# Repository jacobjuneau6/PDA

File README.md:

# ESP32-S3 PDA

A simple ESP32-S3 based phone companion and pocket computer. This open-source hardware project includes a custom PCB, 3D-printable case, and Arduino firmware — everything you need to build a portable device with a color TFT display, LiPo battery management, and physical navigation buttons.

## Features

- **ESP32-S3-WROOM-1-N16R8** module (16 MB flash, 8 MB PSRAM)
- **ST7789 240×320 TFT** color display with PWM backlight control
- **MAX17048** LiPo fuel gauge for accurate battery state-of-charge
- **MCP73831** Li-Ion/Li-Po battery charger (charges via USB)
- **WS2812/NeoPixel** RGB status LED
- **3 navigation buttons** (UP, SELECT, DOWN) with active-low pull-ups
- **USB micro-B** connector for power and data
- **2-layer PCB** with Gerber files ready for fabrication
- **3D-printable case** designed in FreeCAD

## Pinout

| Silkscreen | GPIO | Function |
|-----------|------|----------|
| SCL | 2 | SPI SCLK (TFT clock) |
| SDA | 1 | SPI MOSI (TFT data) |
| CS | 3 | TFT chip select |
| DC | 4 | TFT data/command |
| RST | 5 | TFT reset |
| BL | 6 | TFT backlight PWM |
| — | 7 | WS2812 status LED (NeoPixel) |
| — | 8 | I2C SCL (MAX17048 fuel gauge) |
| — | 9 | I2C SDA (MAX17048 fuel gauge) |
| — | 10 | Button UP |
| — | 11 | Button SELECT |
| — | 12 | Button DOWN |

**Display connector:** 1×08 pin header (GND, VCC, SCL, SDA, RST, DC, CS, BL) for ST7789 240×320 TFT, 1.54″ or 1.69″ diagonal.

**I²C address:** MAX17048 at `0x36`.

## Bill of Materials

| Reference            | Qty | Part                    | DigiKey P/N              | Description                                                | Price  |
|---------------------|-----|-------------------------|--------------------------|------------------------------------------------------------|--------|
| J1                  | 1   | RAHMB20AUETR            | 137-RAHMB20AUETRCT-ND    | USB micro-B receptacle, right-angle, SMT (Switchcraft)     |        |
| LED1                | 1   | COM-16347               | 568-16347CT-ND           | WS2812/NeoPixel RGB LED                                    |        |
| R1, R2              | 2   | RC1206FR-132KL          | 13-RC1206FR-132KLCT-ND   | 2 kΩ 1206 thick-film resistor (Yageo)                      |        |
| SW1, SW2, SW3, SW4  | 4   | B3F-1002                | SW401-ND                 | Tactile switch (Omron)                                      |        |
| U1                  | 1   | ESP32-S3-WROOM-1-N16R8  | 5407-ESP32-S3-WROOM-1-N16R8CT-ND | ESP32-S3 module, 16 MB flash, 8 MB PSRAM        |        |
| U2                  | 1   | MCP73831T-2DCI/MC       | MCP73831T-2DCI/MCCT-ND   | Li-Ion/Li-Po battery charger IC (Microchip)               |        |
| U3                  | 1   | TPS74533PCQWDRVRQ1      | 296-TPS74533PCQWDRVRQ1CT-ND | 3.3 V LDO voltage regulator, 500 mA (TI)              |        |
| U4                  | 1   | MAX17048G+T10           | MAX17048G+T10CT-ND       | LiPo fuel gauge IC (Maxim Integrated)                      |        |
| U5                  | 1   | AO3400A                 | 785-1000-1-ND            | N-channel MOSFET, SOT-23 (battery protection)              |        |
| —                   | 1   | Custom PCB & stencil     | JLCPCB                   | Fabrication                                                | $20.00 |
| —                   | 1   | DigiKey components      |                          | Components & shipping                                      | $30.00 |
| —                   | 1   | 1Ah battery             |                          | https://www.amazon.com/dp/B0DPZVBKMY?th=1                  | $8.00  |
| —                   | 1   | Display                 |                          | https://www.amazon.com/gp/product/B0DFWLD38D/ref=ox_sc_act_title_2?smid=A2UYBS1CH53PM5 | $16.00 |

## Pictures

## Power Architecture

```
USB VBUS (5 V)
  ├── MCP73831 charger (U2) ──→ VBAT (battery voltage)
  │     ├── AO3400A MOSFET (U5) — battery protection
  │     └── MAX17048 fuel gauge (U4) — I²C monitoring
  │
  └── TPS74533 LDO (U3) ──→ 3.3 V rail
        ├── ESP32-S3 module (U1)
        ├── Display backlight (PWM on GPIO6)
        └── Peripherals (WS2812, buttons, I²C pull-ups)
```

- The device charges a single-cell LiPo battery via USB at 4.2 V termination.
- Battery voltage and state-of-charge are monitored by the MAX17048 over I²C.
- The 3.3 V LDO powers the MCU and peripherals from either USB or battery.

## Repository Structure

```
PDA/
├── README.md              # This file
├── BOM.csv                # Bill of Materials with DigiKey part numbers
├── Journal.md             # Design journal — case design notes & images
├── LICENSE                # MIT License
│
├── board/                 # KiCad PCB design
│   ├── board.kicad_sch    # Schematic
│   ├── board.kicad_pcb    # PCB layout
│   ├── board.kicad_pro    # Project settings
│   ├── gbrs/              # Gerber files (ready for fabrication)
│   └── staging/           # Vendor symbols, footprints, and 3D models
│
├── CAD/                   # FreeCAD mechanical design
│   ├── Assembly.FCStd     # Full assembly (PCB + case + battery + display)
│   ├── case.FCStd         # 3D-printable enclosure
│   ├── battery.FCStd      # Dummy battery model (fit check)
│   ├── display.FCStd      # Dummy display model (fit check)
│   └── PCB.step           # PCB STEP export
│
└── CODE/                  # Firmware
    └── test/
        ├── platformio.ini # PlatformIO build configuration
        └── src/
            └── main.cpp   # Arduino demo sketch
```

## Firmware

The demo firmware exercises all major subsystems: display, battery gauge, status LED, and buttons.

### Build & Flash

**Prerequisites:** [PlatformIO](https://platformio.org/install) (VS Code extension or CLI).

```bash
cd CODE/test

# Build
pio run

# Flash and open serial monitor (115200 baud)
pio run --target upload --target monitor
```

### What the Demo Does

1. **Boot splash** — "ESP32-S3 PDA / Boot OK" on the TFT, WS2812 glows blue
2. **Battery readout** — cell voltage and state-of-charge, updates ~6× per second
3. **Button indicators** — shows pressed button (UP/SELECT/DOWN) on the TFT
4. **LED feedback** — WS2812 colour changes:
   - Purple = idle
   - Green = SELECT
   - Red = UP
   - Blue = DOWN
5. **Serial debug** — prints voltage, SOC, and button state at 115200 baud

### Libraries

| Library | Version |
|---------|---------|
| Adafruit GFX | ≥1.11 |
| Adafruit ST7735/ST7789 | ≥1.10 |
| Adafruit MAX1704X | ≥1.0 |
| FastLED | ≥3.7 |

All are fetched automatically by PlatformIO via `lib_deps`.

### Board Configuration

| Setting | Value |
|---------|-------|
| Board | ESP32-S3 DevKitC-1 |
| Framework | Arduino |
| Monitor baud | 115200 |

### Customisation

- **Backlight level** — call `backlightWrite(0..255)` in `loop()` (e.g., dim after inactivity)
- **Rotation** — change `tft.setRotation(1)` (0–3) if your panel is mounted differently
- **I²C pins** — edit `I2C_SDA` and `I2C_SCL` at the top of `main.cpp`

## PCB

- **Layers:** 2-layer board
- **Software:** KiCad 8
- **Gerber files:** Ready for fabrication in [`board/gbrs/`](board/gbrs/)
- **View online:** [Kicanvas](https://kicanvas.org/?github=https://github.com/jacobjuneau6/PDA/blob/main/board/board.kicad_pcb) — interactive board viewer (no KiCad install needed)

The PCB uses all surface-mount components. Most ICs are in small-outline packages (SOT-23, TDFN, WSON). The display connects via a standard 1×08 2.54 mm pitch pin header.

## Case

Designed in FreeCAD with a boxy, sharp-edged aesthetic. The case holds:
- The custom PCB
- A single-cell LiPo battery
- The ST7789 TFT display (1.54″ or 1.69″)

Dummy battery and display models are included for fit checking in the assembly.

## License

MIT License — see [LICENSE](LICENSE) for details.

Copyright (c) 2026 jacobjuneau6

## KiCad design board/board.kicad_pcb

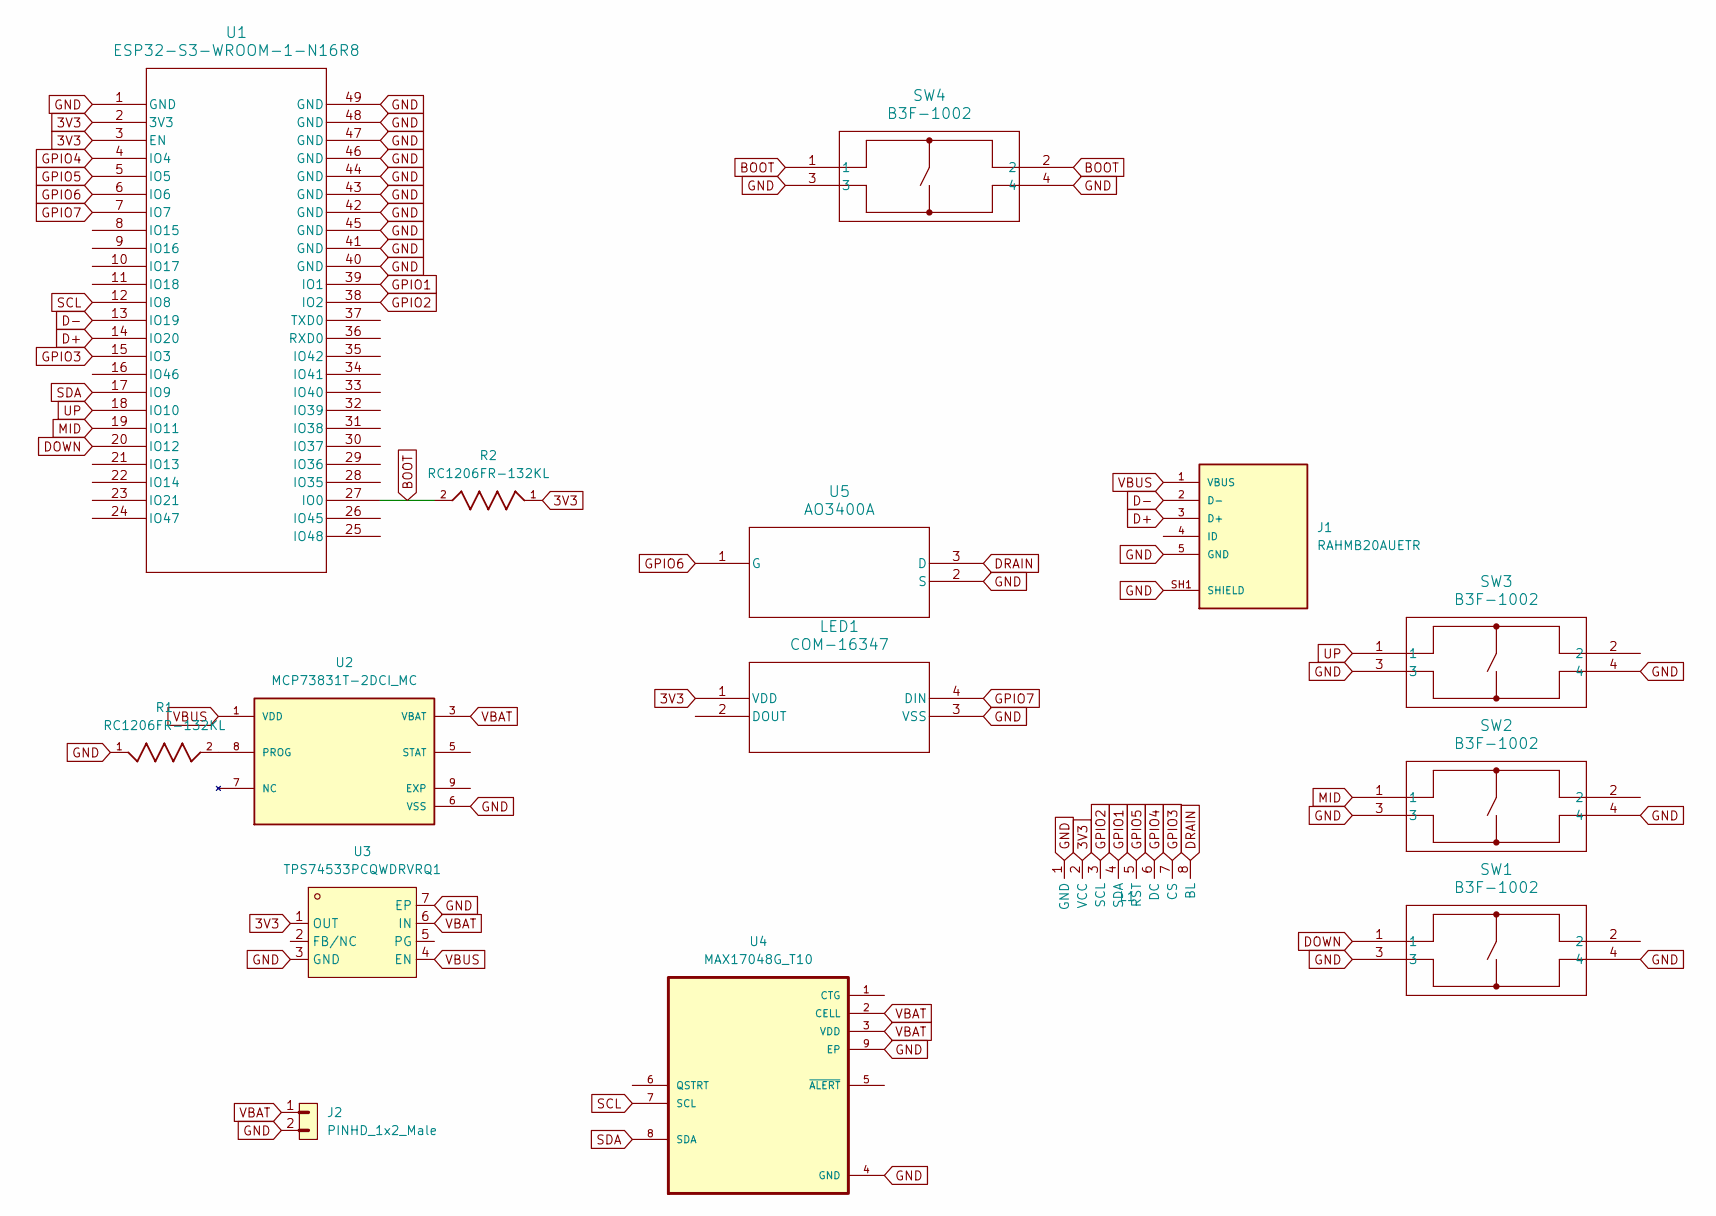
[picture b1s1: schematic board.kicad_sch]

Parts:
J1: RAHMB20AUETR; SWITCHCRAFT_RAHMB20AUETR; PARTREV A; DigiKey_Part_Number 137-RAHMB20AUETRCT-ND
J2: PINHD_1x2_Male; PinHeader_1x02_P2.54mm_Vertical_SMD_Pin1Left
L1: PinHeader_1x08_P2.54mm_Vertical
LED1: COM-16347; COM-16347_SPK; DigiKey_Part_Number 568-16347CT-ND
R1, R2: RC1206FR-132KL; RESC3216X65; DigiKey_Part_Number 13-RC1206FR-132KLCT-ND
SW1, SW2, SW3, SW4: B3F-1002; SW_B3F-1000_OMR; DigiKey_Part_Number SW401-ND
U1: ESP32-S3-WROOM-1-N16R8; ESP32-S3-WROOM-1_EXP; DigiKey_Part_Number 5407-ESP32-S3-WROOM-1-N16R8CT-ND
U2: MCP73831T-2DCI_MC; SON50P200X200X80-9N; PARTREV H; DigiKey_Part_Number MCP73831T-2DCI/MCCT-ND
U3: TPS74533PCQWDRVRQ1; WSON-6_L2.0-W2.0-P0.65-TL-EP; MPN TPS74533PCQWDRVRQ1; LCSC Part C2860924
U4: MAX17048G_T10; SON50P200X200X80-9N; DigiKey_Part_Number MAX17048G+T10CT-ND
U5: AO3400A; SOT-23; DigiKey_Part_Number 785-1000-1-ND

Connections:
3V3: L1.2 (VCC), LED1.1 (VDD), R2.1, U1.2 (3V3), U1.3 (EN), U3.1 (OUT)
BOOT: R2.2, SW4.1, SW4.2, U1.27 (IO0)
D+: J1.3 (D+), U1.14 (IO20)
D-: J1.2 (D-), U1.13 (IO19)
DOWN: SW1.1, U1.20 (IO12)
DRAIN: L1.8 (BL), U5.3 (D)
GND: J1.5 (GND), J1.SH1 (SHIELD), J1.SH2 (SHIELD), J1.SH3 (SHIELD), J1.SH4 (SHIELD), J1.SH5 (SHIELD), J1.SH6 (SHIELD), J2.2, L1.1 (GND), LED1.3 (VSS), R1.1, SW1.3, SW1.4, SW2.3, SW2.4, SW3.3, SW3.4, SW4.3, SW4.4, U1.1 (GND), U1.40 (GND), U1.41 (GND), U1.42 (GND), U1.43 (GND), U1.44 (GND), U1.45 (GND), U1.46 (GND), U1.47 (GND), U1.48 (GND), U1.49 (GND), U2.6 (VSS), U3.3 (GND), U3.7 (EP), U4.4 (GND), U4.9 (EP), U5.2 (S)
GPIO1: L1.4 (SDA), U1.39 (IO1)
GPIO2: L1.3 (SCL), U1.38 (IO2)
GPIO3: L1.7 (CS), U1.15 (IO3)
GPIO4: L1.6 (DC), U1.4 (IO4)
GPIO5: L1.5 (RST), U1.5 (IO5)
GPIO6: U1.6 (IO6), U5.1 (G)
GPIO7: LED1.4 (DIN), U1.7 (IO7)
MID: SW2.1, U1.19 (IO11)
unnamed: R1.2, U2.8 (PROG)
SCL: U1.12 (IO8), U4.7 (SCL)
SDA: U1.17 (IO9), U4.8 (SDA)
UP: SW3.1, U1.18 (IO10)
VBAT: J2.1, U2.3 (VBAT), U2.4 (VBAT), U3.6 (IN), U4.2 (CELL), U4.3 (VDD)
VBUS: J1.1 (VBUS), U2.1 (VDD), U2.2 (VDD), U3.4 (EN)

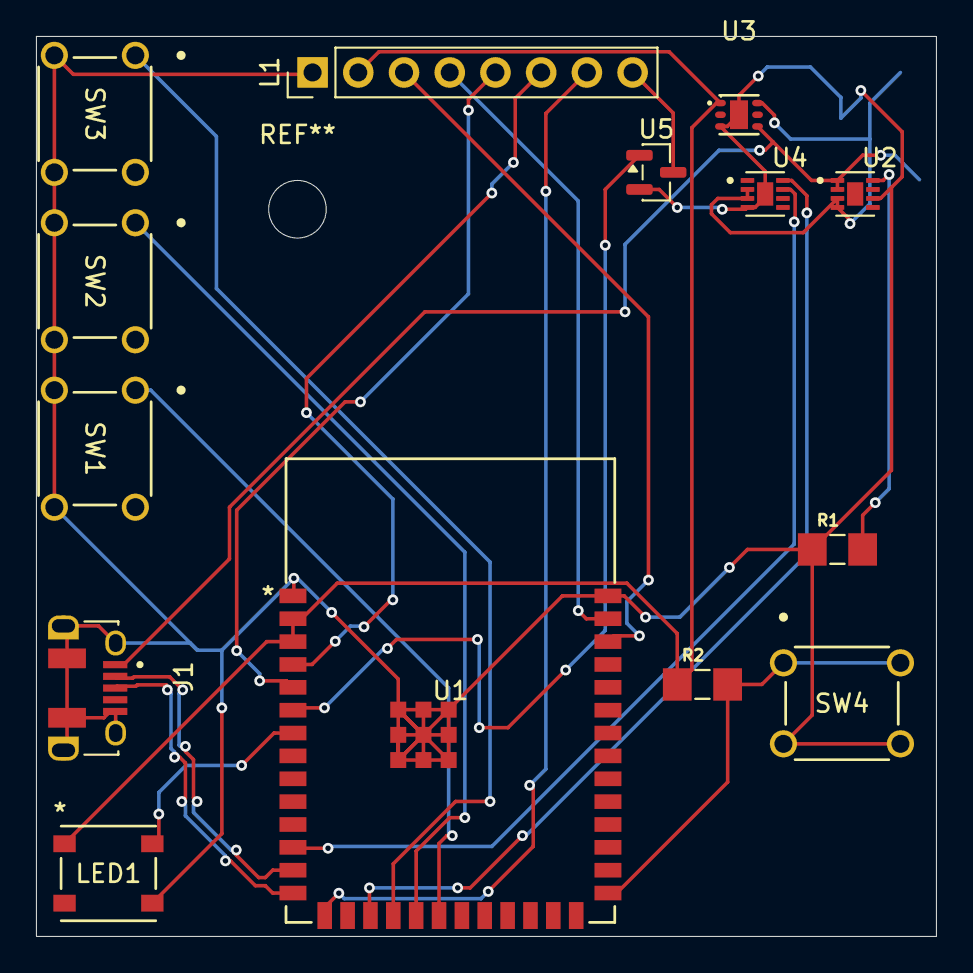
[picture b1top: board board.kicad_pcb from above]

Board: 2 copper layers, 50.0 x 50.0 mm, 15 parts (1 on the bottom side), 21 nets.

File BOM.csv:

"Reference","Qty","DigiKey_Part_Number"
"J1","1","137-RAHMB20AUETRCT-ND"
"LED1","1","568-16347CT-ND"
"R1,R2","2","13-RC1206FR-132KLCT-ND"
"SW1,SW2,SW3,SW4","4","  SW401-ND"
"U1","1","5407-ESP32-S3-WROOM-1-N16R8CT-ND "
"U2","1","MCP73831T-2DCI/MCCT-ND"
"U3","1","296-TPS74533PCQWDRVRQ1CT-ND "
"U4","1","MAX17048G+T10CT-ND"
"U5","1","785-1000-1-ND"

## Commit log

2026-06-29 ADD PCB & CAD
2026-06-29 Add project title and description to README
2026-06-29 Add journal entry for PCB case design and images
    Documented the case design for the PCB assembly, including fit checks and design choices. Added images of the design for reference.
2026-06-29 add basic test code
2026-06-29 add gerbers and BOM
2026-06-29 Enhance Bill of Materials with pricing details
    Updated the Bill of Materials table to include prices and additional components.
2026-06-29 add Kicanvas
2026-06-29 Add pictures section to README
    Added a section for pictures with multiple images to the README.
